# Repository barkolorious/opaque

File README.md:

# **OPAQUE**: **O**pen-source **P**ortable **A**ir **QU**ality **E**quipment

---

A portable device that measures the temperature, humidity, AQI (Air Quality Index), tVOC (total Volatile Organic Components), eCO2, CO, NH3, NOx and O3 amount in the air.

It comes in 2 flavours: OPAQUE Lite and OPAQUE Connect. OPAQUE Lite stores the measurements on device, in contrast to OPAQUE Connect, which stores data both on device and on cloud. OPAQUE Connect can also pull data from cloud.

It's still work in progress.

2204-D Report: https://docs.google.com/document/d/112pA8oVNO5BkxKRDr9aJxBSNs7QlX5zvWhuIxiFPKnI/edit?usp=sharing

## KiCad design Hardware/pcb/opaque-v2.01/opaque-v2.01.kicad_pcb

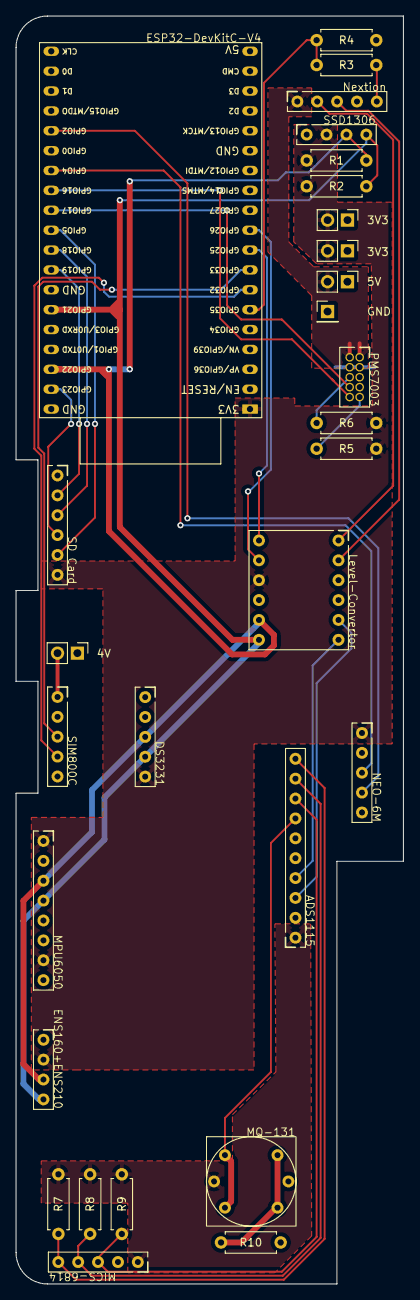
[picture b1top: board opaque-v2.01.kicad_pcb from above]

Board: 2 copper layers, 49.5 x 162.0 mm, 29 parts (0 on the bottom side), 31 nets.

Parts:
J1: Conn_01x01_Socket; PinHeader_1x01_P2.54mm_Vertical
J2, J3, J4, J5: Conn_01x02_Pin; PinHeader_1x02_P2.54mm_Vertical
R1, R2: 3.3kΩ; R_Axial_DIN0207_L6.3mm_D2.5mm_P7.62mm_Horizontal
R3: 5.6kΩ; R_Axial_DIN0207_L6.3mm_D2.5mm_P7.62mm_Horizontal
R4, R5, R6: 10kΩ; R_Axial_DIN0207_L6.3mm_D2.5mm_P7.62mm_Horizontal
R7, R8, R9: 47kΩ; R_Axial_DIN0207_L6.3mm_D2.5mm_P7.62mm_Horizontal
R10: 1MΩ; R_Axial_DIN0207_L6.3mm_D2.5mm_P7.62mm_Horizontal
U1: ESP32-DevKitC
U2: DS3231
U3: MPU6050
U4: ENS160+ENS210
U5: SIM800C
U6: SD_Card
U7: NEO-6M
U8: SSD1306
U9: Level-Convertor
U10: ADS1115
U11: NX4827P043
U12: PMS7003
U13: MICS-6814
U14: MQ-131

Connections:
3V3: J4.2, J5.2, R1.1, R2.1, R5.1, R6.1, U1.1 (3V3), U2.5 (VCC), U3.1 (VCC), U3.7 (AD0), U4.2 (VCC), U6.6 (VCC), U7.1 (VCC), U8.2 (VCC), U9.9 (LV)
4V: J3.2, U5.1 (VCC)
5V: J2.2, R7.2, R8.2, R9.2, U9.3 (HV), U10.1 (VCC), U11.1 (VCC), U12.1 (VCC), U12.2 (VCC), U13.1 (VCC), U14.2 (Heater)
CLK: U1.30 (GPIO18), U6.3 (CLK)
GND: J1.1, R4.1, R10.2, U1.14 (GND), U1.32 (GND), U1.38 (GND), U2.1 (GND), U3.2 (GND), U4.1 (GND), U5.5 (GND), U6.1 (GND), U7.2 (GND), U8.1 (GND), U9.4 (GND), U9.10 (GND), U10.2 (GND), U11.4 (GND), U12.3 (GND), U12.4 (GND), U13.2 (GND), U14.5 (Heater)
INT_{Nextion}: R3.1, R4.2, U1.6 (VDET_2/GPIO35/ADC1_CH7)
MISO: U1.31 (GPIO19), U6.2 (MISO)
MOSI: U1.37 (GPIO23), U6.4 (MOSI)
unnamed: R10.1, U14.4 (Load), U14.6 (Load)
unnamed: U10.7 (A0), U14.1 (Load), U14.3 (Load)
unnamed: R9.1, U10.8 (A1), U13.3 (NO2)
unnamed: R8.1, U10.9 (A2), U13.4 (NH3)
unnamed: R7.1, U10.10 (A3), U13.5 (CO)
unnamed: U9.5 (HV3), U10.3 (SCL)
unnamed: U9.6 (HV4), U10.4 (SDA)
unnamed: R3.2, U11.5 (INT)
unnamed: U9.2 (HV2), U11.3 (RXD)
unnamed: U9.1 (HV1), U11.2 (TXD)
unnamed: R6.2, U12.5 (RESET)
unnamed: R5.2, U12.10 (SET)
RX_{NEO-6M}: U1.24 (ADC2_CH2/GPIO2), U7.4 (RXD)
RX_{Nextion}: U1.10 (DAC_2/ADC2_CH9/GPIO26), U9.8 (LV2)
RX_{PMS7003}: U1.28 (GPIO17), U12.7 (RX)
RX_{SIM800C}: U1.8 (32K_XN/GPIO33/ADC1_CH5), U5.3 (RXD)
SCL: R1.2, U1.36 (GPIO22), U2.3 (SCL), U3.3 (SCL), U4.3 (SCL), U8.3 (SCL), U9.11 (LV3)
SDA: R2.2, U1.33 (GPIO21), U2.4 (SDA), U3.4 (SDA), U4.4 (SDA), U8.4 (SDA), U9.12 (LV4)
TX_{NEO-6M}: U1.26 (ADC2_CH0/GPIO4), U7.3 (TXD)
TX_{Nextion}: U1.9 (DAC_1/ADC2_CH8/GPIO25), U9.7 (LV1)
TX_{PMS7003}: U1.27 (GPIO16), U12.9 (TX)
TX_{SIM800C}: U1.7 (32K_XP/GPIO32/ADC1_CH4), U5.4 (TXD)
~CS_{SD}: U1.29 (GPIO5), U6.5 (~CS)

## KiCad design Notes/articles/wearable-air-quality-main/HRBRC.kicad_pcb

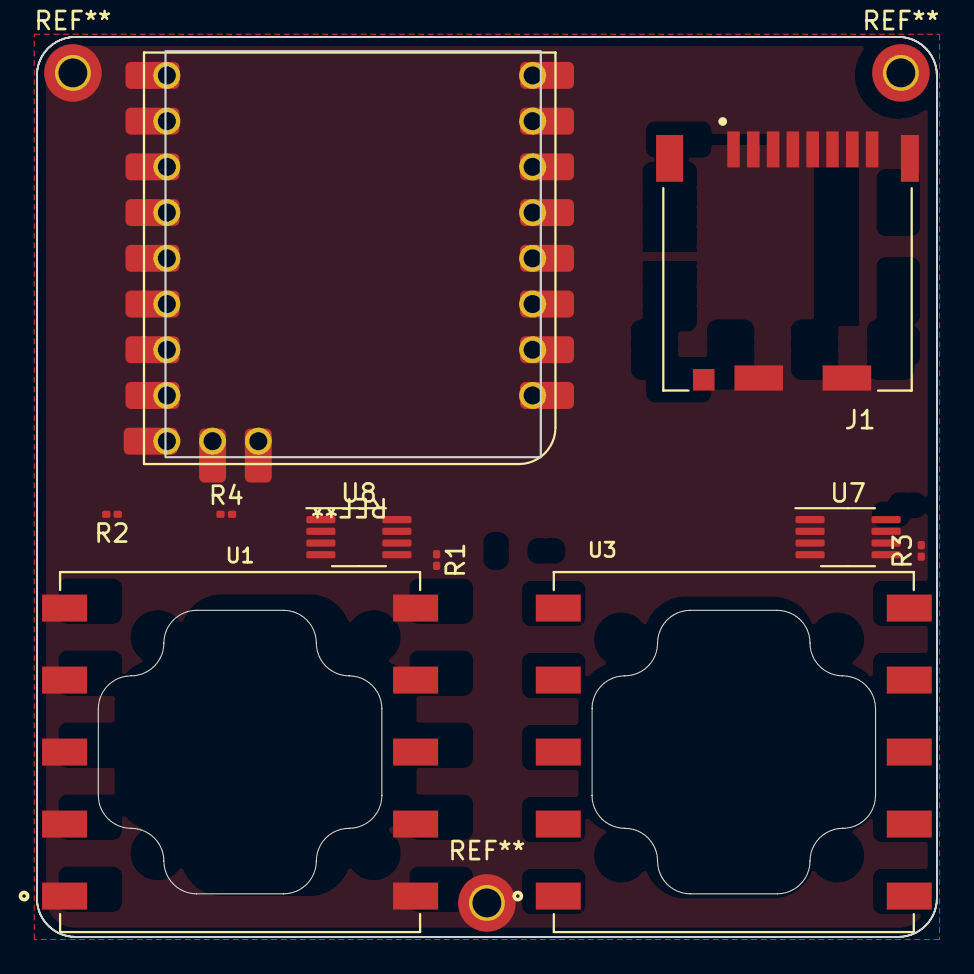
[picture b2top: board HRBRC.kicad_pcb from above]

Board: 2 copper layers, 50.0 x 50.0 mm, 10 parts (1 on the bottom side), 11 nets, no tracks yet.

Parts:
J1: Micro_SD_Card_Det_Hirose_DM3CS; HRS_DM3CS-SF
R1, R3: 49.9; R_0201_0603Metric
R2, R4: 499K; R_0201_0603Metric
U1, U3: 110-407; XDCR_110-407
U6: SCD41; SCD4x
U7, U8: MCP6L02x-xMS; MSOP-8_3x3mm_P0.65mm

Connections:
+3.3VA: U7.8 (V+), U8.8 (V+)
+3V3: J1.4 (VDD), U6.7 (VDD), U6.19 (VDDH)
GND: U6.6 (GND), U6.20 (GND), U6.21 (GND), U7.4 (V-), U8.4 (V-)
unnamed: U8.1, U8.5 (+)
unnamed: J1.6 (VSS), J1.9 (DET_B)
unnamed: R1.1, U1.6 (COUNTER)
unnamed: R3.1, U3.6 (COUNTER)
unnamed: U7.6 (-), U7.7
unnamed: U1.1 (WORKING), U1.10 (WORKING)
unnamed: U3.1 (WORKING), U3.10 (WORKING)
VGAS: U8.6 (-), U8.7

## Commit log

2025-02-01 First commit.
2025-02-01 Tidied up.
2025-02-01 Added README.md
2025-04-13 Writtin code
2025-05-06 Finished code?
2025-07-01 Changed a lot could be final
2025-12-07 Changed more
